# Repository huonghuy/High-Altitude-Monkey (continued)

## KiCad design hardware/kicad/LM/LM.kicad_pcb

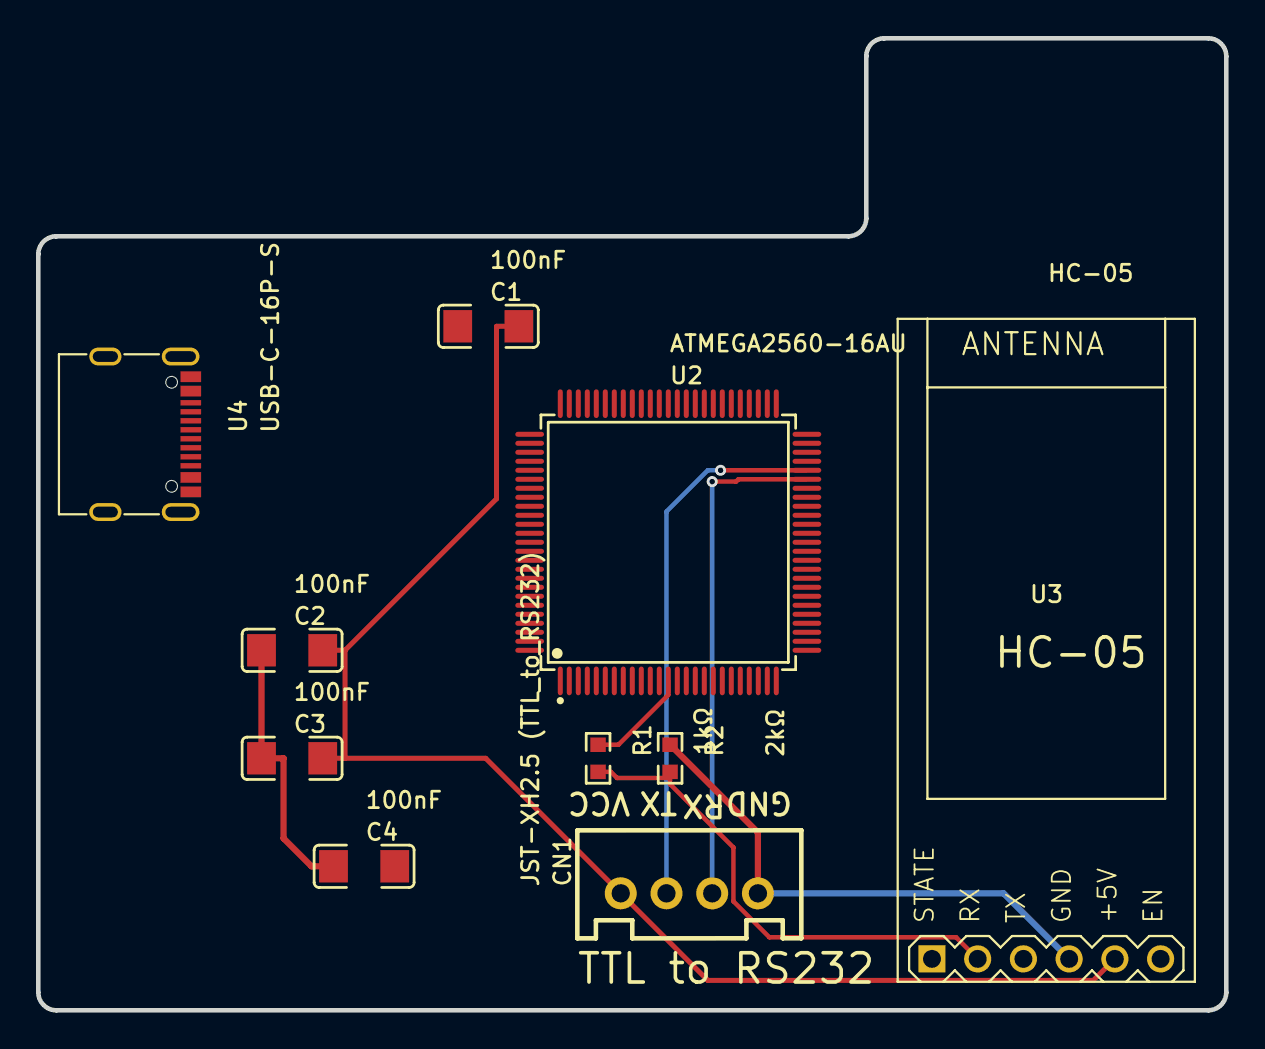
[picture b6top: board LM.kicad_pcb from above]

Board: 2 copper layers, 66.0 x 54.0 mm, 10 parts (0 on the bottom side), 8 nets.

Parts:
C1, C2, C3, C4: 100nF; SMD 1206 CAPACITOR
CN1: JST-XH2.5 (TTL_to_RS232); 4PIN_2.54_MM_JST_XHP_JST_CONNECTOR_FOR_DC_SOCKET
R1: 1kΩ; R0603
R2: 2kΩ; R0603
U2: ATMEGA2560-16AU; TQFP-100_L14.0-W14.0-P0.50-LS16.0-BL
U3: HC-05; WIRELESS-BLUETOOTH-HC-05
U4: USB-C-16P-S

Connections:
+5V: C1.2, C2.2, C3.2, CN1.1, U2.10, U2.31, U2.61, U2.80, U2.100, U3.5
D16(TX2): R1.1, U2.13
D17(RX2): U2.12, U3.3
D18(TXD): CN1.2, U2.46
D19(RXD): CN1.3, U2.45
GND: C1.1, C2.1, C3.1, C4.1, CN1.4, R2.1, U2.11, U2.32, U2.62, U2.81, U2.99, U3.4
U2_98: C4.2, U2.98
U3_2: R1.2, R2.2, U3.2

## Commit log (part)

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2026-04-30 refactor fr fr, also got rid of unneeded files
